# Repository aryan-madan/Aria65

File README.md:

.png)

# Name

Meraki, is a greek word that means 'to do something with soul, creativity, or love; leaving a piece of yourself in what you do'.

# Layout 

The keyboard has a 65% WKL Layout. WKL stands for win-key-less, where the Windows key is removed from the keyboard, to give it a more symmetrical shape. WKL's are rarely seen in 65% form, which inspired me to make this board. I also opted for a blocker at the top right to fit the MCU.

# Firmware

The Meraki65 uses qmk for its firmware.
I also created a web-based software to re-map keys, called [Keydeck](https://keydeck.xyz).

# PCB

## Schematic

.png)

## PCB

# Bill of Materials

Total Cost: **9,792** (~$106.38 USD)

## Case

https://app.shapr3d.com/v/_-Txvu9VtqTR88f_0C18B

To be 3d printed by the Printing Legion.

## Parts

| Piece | Brand | Quantity | Cost (INR) | Cost (USD) | Link |
|-------|-------|----------|-----------|-----------|------|
| Plate Mount Stabilizers | Durock | 1 set | 380 | ~$4.13 | [Link](https://www.genesispc.in/products/durock-plate-mount-stabilizers-6-25u-4x2u-black?variant=43129560924213) |
| Y2 Switches | Keygeek | 70 | 2240 | ~$24.35 | [Link](https://keyora.store/products/keygeek-y2-linear-switch) |
| Gummy-O-Ring Mount | NeoMacro | 1 | 650 | ~$7.00 | [Link](https://neomacro.in/products/neo65-spare-parts-pre-order?variant=46159065415958) |
| M2 x 12mm Screws | Generic | 2 | — | — | - |
| M2 x 10mm Screws | Generic | 2 | — | — | - |
| **Total** | | | **3522** | **~$38.22** | |

## PCB

| Part | Brand | Quantity | Cost (INR) | Cost (USD) | Link |
|------|-------|----------|-----------|-----------|------|
| Printing | JLCPCB | 5(min) | 3403 | ~$37.00 | [Link](https://jlcpcb.com/) |
| RP 2040 Zero | Robu | 1 | 235 | ~$2.55 | [Link](https://robu.in/product/rp2040-zero-for-raspberry-pi-microcontroller-with-soldering/) |
| Hotswap Sockets | Kailh | 100(min) | 532 | ~$5.78 | [Link](https://meckeys.com/shop/accessories/keyboard-accessories/key-switches/kailh-hot-swap-socket/) |
| Diodes | — | 100(min) | 100 | ~$1.09 | [Link](https://www.amazon.in/dp/B084ZP5BJ3?ref=cm_sw_r_cp_ud_dp_YPW3WFYTE31QA18570D1&social_share=cm_sw_r_cp_ud_dp_YPW3WFYTE31QA18570D1&_encoding=UTF8&psc=1) |
| **Total** | | | **4270** | **~$46.42** | |

## Decoration

| Part | Brand | Quantity | Cost (INR) | Cost (USD) |
|------|-------|----------|-----------|-----------|
| Keycaps | Clones | 1 set | 2000 | ~$21.74 |
| **Total** | | | **2000** | **~$21.74** |

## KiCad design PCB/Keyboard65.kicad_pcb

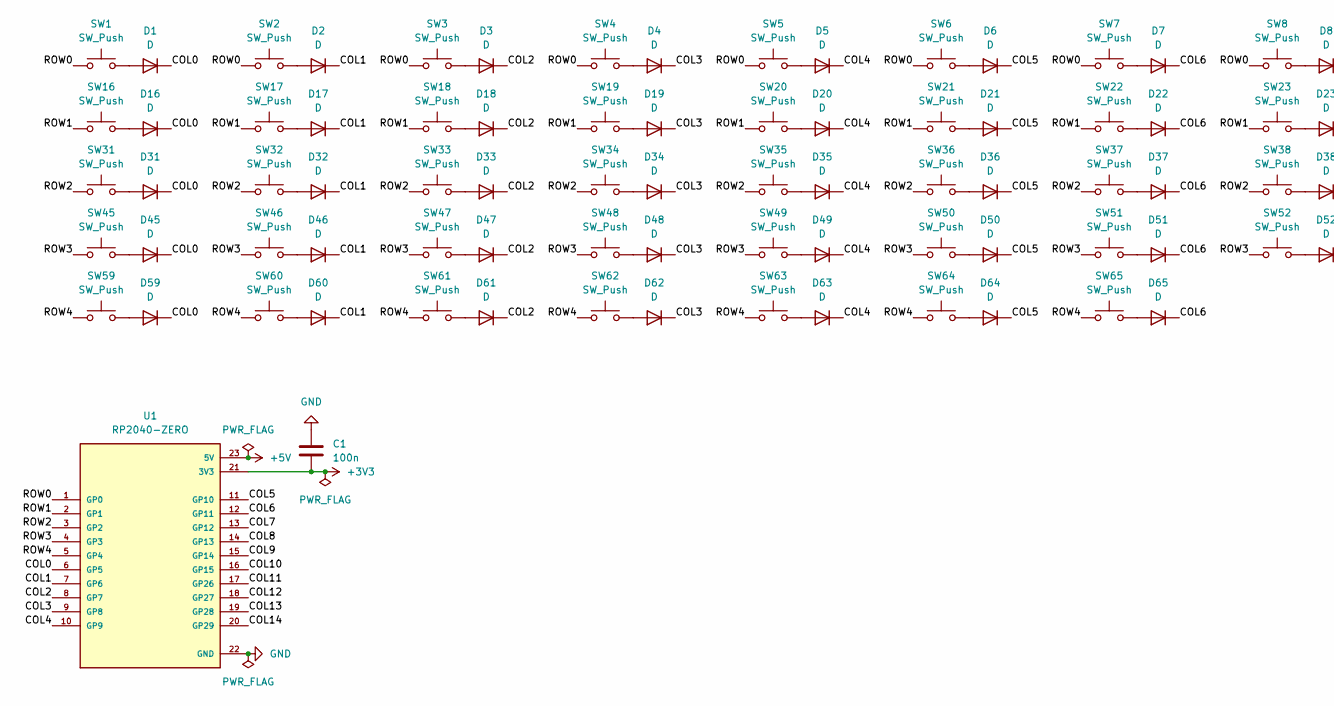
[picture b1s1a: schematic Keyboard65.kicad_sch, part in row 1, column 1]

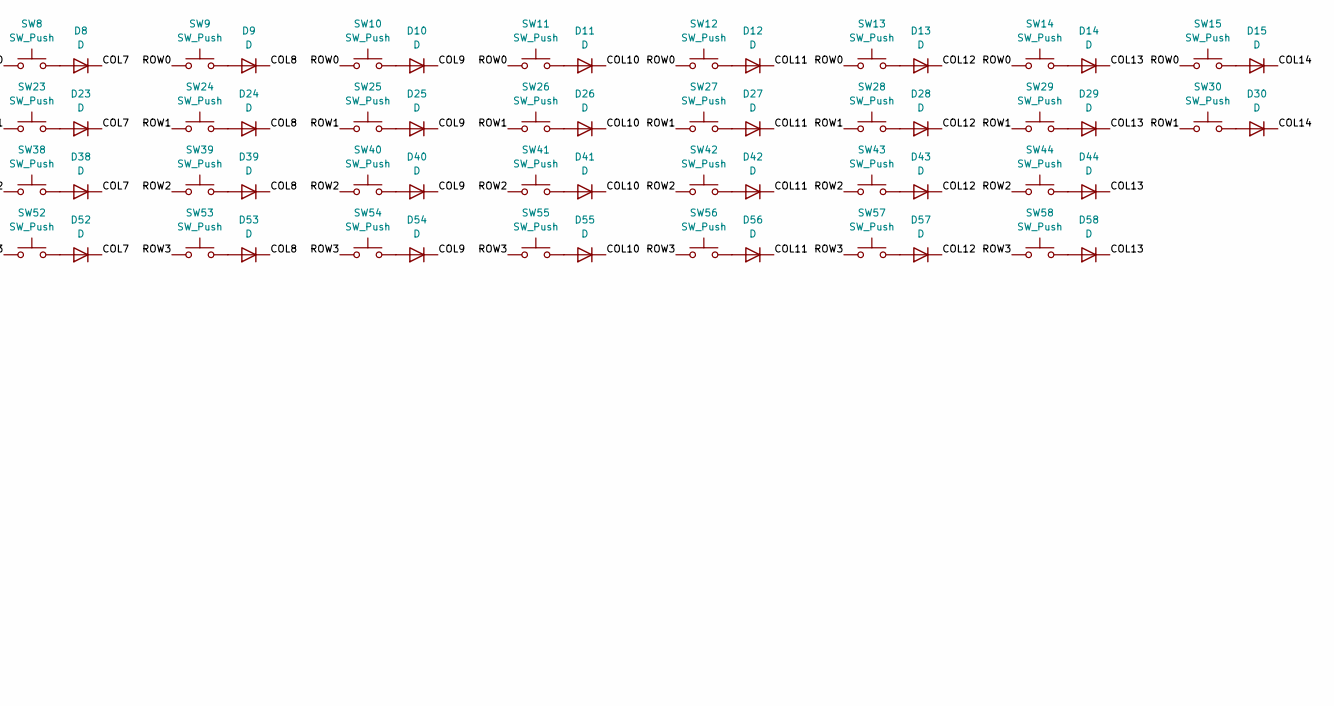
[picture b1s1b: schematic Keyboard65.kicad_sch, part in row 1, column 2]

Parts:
C1: 100n; C_0805_2012Metric
D1, D2, D3, D4, D5, D6, D7, D8, D9, D10, D11, D12, D13, D14, D15, D16, D17, D18, D19, D20, D21, D22, D23, D24, D25, D26, D27, D28, D29, D30, D31, D32, D33, D34, D35, D36, D37, D38, D39, D40, D41, D42, D43, D44, D45, D46, D47, D48, D49, D50, D51, D52, D53, D54, D55, D56, D57, D58, D59, D60, D61, D62, D63, D64, D65: D; D_SOD-123
SW1, SW2, SW3, SW4, SW5, SW6, SW7, SW8, SW9, SW10, SW11, SW12, SW13, SW14, SW15, SW16, SW17, SW18, SW19, SW20, SW21, SW22, SW23, SW24, SW25, SW26, SW27, SW28, SW29, SW30, SW31, SW32, SW33, SW34, SW35, SW36, SW37, SW38, SW39, SW40, SW41, SW42, SW43, SW44, SW45, SW46, SW47, SW48, SW49, SW50, SW51, SW52, SW53, SW54, SW55, SW56, SW57, SW58, SW59, SW60, SW61, SW62, SW63, SW64, SW65: SW_Push; MX-Hotswap-1U
U1: RP2040-ZERO; MODULE_RP2040-ZERO; PARTREV NA

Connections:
+3V3: C1.1, U1.21 (3V3)
+5V: U1.23 (5V)
/COL0: D1.1 (K), D16.1 (K), D31.1 (K), D45.1 (K), D59.1 (K), U1.6 (GP5)
/COL1: D2.1 (K), D17.1 (K), D32.1 (K), D46.1 (K), D60.1 (K), U1.7 (GP6)
/COL2: D3.1 (K), D18.1 (K), D33.1 (K), D47.1 (K), D61.1 (K), U1.8 (GP7)
/COL3: D4.1 (K), D19.1 (K), D34.1 (K), D48.1 (K), D62.1 (K), U1.9 (GP8)
/COL4: D5.1 (K), D20.1 (K), D35.1 (K), D49.1 (K), D63.1 (K), U1.10 (GP9)
/COL5: D6.1 (K), D21.1 (K), D36.1 (K), D50.1 (K), D64.1 (K), U1.11 (GP10)
/COL6: D7.1 (K), D22.1 (K), D37.1 (K), D51.1 (K), D65.1 (K), U1.12 (GP11)
/COL7: D8.1 (K), D23.1 (K), D38.1 (K), D52.1 (K), U1.13 (GP12)
/COL8: D9.1 (K), D24.1 (K), D39.1 (K), D53.1 (K), U1.14 (GP13)
/COL9: D10.1 (K), D25.1 (K), D40.1 (K), D54.1 (K), U1.15 (GP14)
/COL10: D11.1 (K), D26.1 (K), D41.1 (K), D55.1 (K), U1.16 (GP15)
/COL11: D12.1 (K), D27.1 (K), D42.1 (K), D56.1 (K), U1.17 (GP26)
/COL12: D13.1 (K), D28.1 (K), D43.1 (K), D57.1 (K), U1.18 (GP27)
/COL13: D14.1 (K), D29.1 (K), D44.1 (K), D58.1 (K), U1.19 (GP28)
/COL14: D15.1 (K), D30.1 (K), U1.20 (GP29)
/ROW0: SW1.1, SW2.1, SW3.1, SW4.1, SW5.1, SW6.1, SW7.1, SW8.1, SW9.1, SW10.1, SW11.1, SW12.1, SW13.1, SW14.1, SW15.1, U1.1 (GP0)
/ROW1: SW16.1, SW17.1, SW18.1, SW19.1, SW20.1, SW21.1, SW22.1, SW23.1, SW24.1, SW25.1, SW26.1, SW27.1, SW28.1, SW29.1, SW30.1, U1.2 (GP1)
/ROW2: SW31.1, SW32.1, SW33.1, SW34.1, SW35.1, SW36.1, SW37.1, SW38.1, SW39.1, SW40.1, SW41.1, SW42.1, SW43.1, SW44.1, U1.3 (GP2)
/ROW3: SW45.1, SW46.1, SW47.1, SW48.1, SW49.1, SW50.1, SW51.1, SW52.1, SW53.1, SW54.1, SW55.1, SW56.1, SW57.1, SW58.1, U1.4 (GP3)
/ROW4: SW59.1, SW60.1, SW61.1, SW62.1, SW63.1, SW64.1, SW65.1, U1.5 (GP4)
GND: C1.2, U1.22 (GND)
unnamed: D1.2 (A), SW1.2
unnamed: D2.2 (A), SW2.2
unnamed: D3.2 (A), SW3.2
unnamed: D4.2 (A), SW4.2
unnamed: D5.2 (A), SW5.2
unnamed: D6.2 (A), SW6.2
unnamed: D7.2 (A), SW7.2
unnamed: D8.2 (A), SW8.2
unnamed: D9.2 (A), SW9.2
unnamed: D10.2 (A), SW10.2
unnamed: D11.2 (A), SW11.2
unnamed: D12.2 (A), SW12.2
unnamed: D13.2 (A), SW13.2
unnamed: D14.2 (A), SW14.2
unnamed: D15.2 (A), SW15.2
unnamed: D16.2 (A), SW16.2
unnamed: D17.2 (A), SW17.2
unnamed: D18.2 (A), SW18.2
unnamed: D19.2 (A), SW19.2
unnamed: D20.2 (A), SW20.2
unnamed: D21.2 (A), SW21.2
unnamed: D22.2 (A), SW22.2
unnamed: D23.2 (A), SW23.2
unnamed: D24.2 (A), SW24.2
unnamed: D25.2 (A), SW25.2
unnamed: D26.2 (A), SW26.2
unnamed: D27.2 (A), SW27.2
unnamed: D28.2 (A), SW28.2
unnamed: D29.2 (A), SW29.2
unnamed: D30.2 (A), SW30.2
unnamed: D31.2 (A), SW31.2
unnamed: D32.2 (A), SW32.2
unnamed: D33.2 (A), SW33.2
unnamed: D34.2 (A), SW34.2
unnamed: D35.2 (A), SW35.2
unnamed: D36.2 (A), SW36.2
unnamed: D37.2 (A), SW37.2
unnamed: D38.2 (A), SW38.2
unnamed: D39.2 (A), SW39.2
unnamed: D40.2 (A), SW40.2
unnamed: D41.2 (A), SW41.2
unnamed: D42.2 (A), SW42.2
unnamed: D43.2 (A), SW43.2
unnamed: D44.2 (A), SW44.2
unnamed: D45.2 (A), SW45.2
unnamed: D46.2 (A), SW46.2
unnamed: D47.2 (A), SW47.2
unnamed: D48.2 (A), SW48.2
unnamed: D49.2 (A), SW49.2
unnamed: D50.2 (A), SW50.2
unnamed: D51.2 (A), SW51.2
unnamed: D52.2 (A), SW52.2
unnamed: D53.2 (A), SW53.2
unnamed: D54.2 (A), SW54.2
unnamed: D55.2 (A), SW55.2
unnamed: D56.2 (A), SW56.2
unnamed: D57.2 (A), SW57.2
unnamed: D58.2 (A), SW58.2
unnamed: D59.2 (A), SW59.2
unnamed: D60.2 (A), SW60.2
unnamed: D61.2 (A), SW61.2
unnamed: D62.2 (A), SW62.2
unnamed: D63.2 (A), SW63.2
unnamed: D64.2 (A), SW64.2
unnamed: D65.2 (A), SW65.2

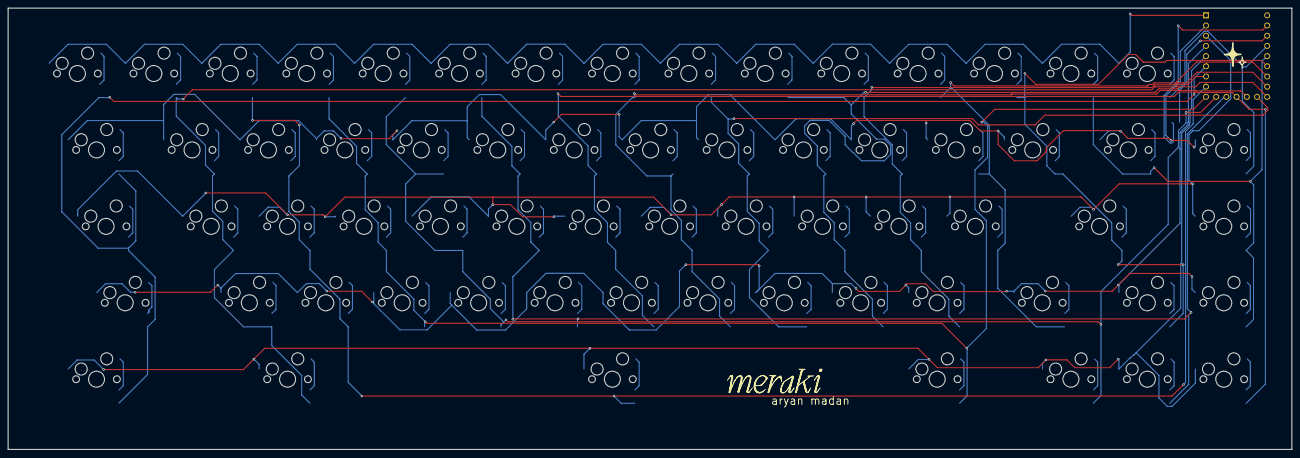
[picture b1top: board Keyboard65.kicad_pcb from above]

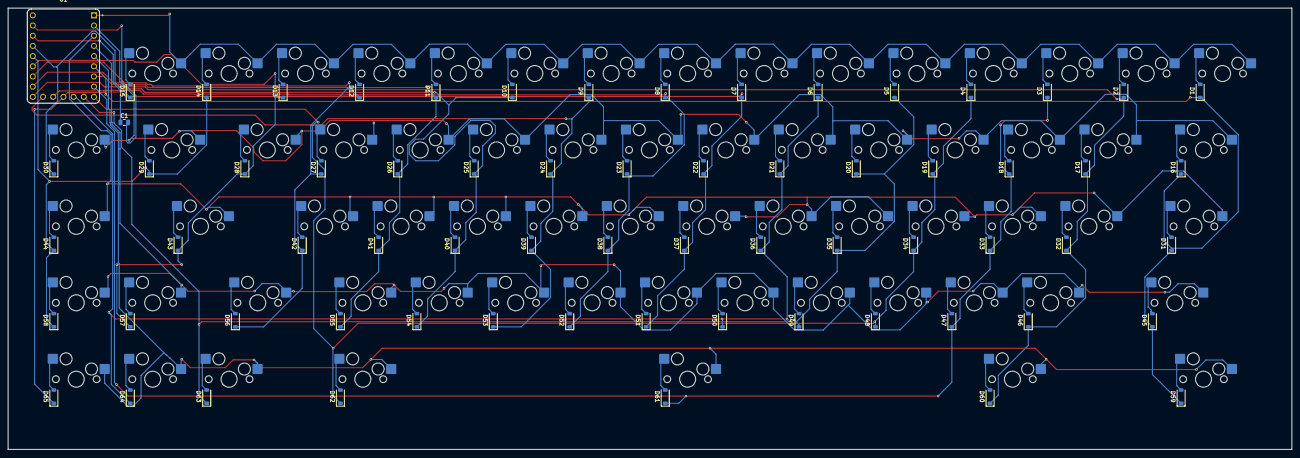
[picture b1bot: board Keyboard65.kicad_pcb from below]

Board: 2 copper layers, 320.0 x 110.0 mm, 132 parts (132 on the bottom side), 87 nets.

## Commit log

2026-03-06 [1] Making the schematics
2026-03-08 [2] I hate routing traces
2026-03-08 [3] Modeling the case
2026-03-09 [4] Building the firmware and the software
2026-03-09 Updated firmware and software to correctly send layer packets
2026-03-12 [5] Complete overhaul
2026-03-12 Fixed README.md
2026-03-12 Fixed README.md (again)
2026-03-12 Changed all mentions of Aria65 to Meraki65
2026-03-12 Added case in README.md
2026-03-12 Added firmware to README.md
2026-03-12 Fixed README.md (again x2)
2026-03-13 Updated README.md with correct BOM
2026-03-14 [5] Finishing touches
2026-03-14 Added BOM.csv file
2026-03-14 Update the silkscreen and the PCB files
2026-03-14 Added project file link and qty field in BOM
